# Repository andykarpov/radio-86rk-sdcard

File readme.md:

# Адаптер SD-CARD для Радио-86РК_SRAM

Данный проект является развитием проекта адаптера SD-CARD  от **Vinxru** 

## Изменения в схеме и печатной плате
- Добавлен LDO регулятор LM1117 3v3
- Вместо резистивных делителей используется буфер HEF4050BT
- добавлен 26-контактный IDC разъем под кабель для сопряжения модуля с Радио-86РК_SRAM
- Добавлен 6-контактный разъем для программатора
- Вместо Atmega8L используется МК Atmega328P

Плата разработана в CAD Eagle 7.0 и выполнена в форм-факторе 5x5 см, что дает возможность заказать ее производство у китайцев. Пробная первая партия была заказана у [http://www.dfrobot.com](http://www.dfrobot.com).

Gerber-файлы для производства платы проходят валидацию по стандартам pcb-сервиса от dfrobot.com.

## Фото готового устройства

## BOM-list

Микросхемы:

- U1 - Atmega8L(A) (или Atmega328P, или аналогичный МК)

- U2 - HEF4050BT (или другого производителя, 4050 в SMD-корпусе)

- IC1 - LM1117-3.3V

Разъемы:

- CONN1 - 4UCon 19646 или аналогичный ([pdf](http://www.4uconnector.com/online/object/4udrawing/19608.pdf), [Sparkfun](https://www.sparkfun.com/products/12769), [noname разъем на ebay](http://www.ebay.com/itm/5-Pcs-SD-Memory-Card-Sockets-Connectors-Replacements-29-x-28-5-x-2-5mm-/291005194440?pt=UK_BOI_Electrical_Components_Supplies_ET&hash=item43c142e0c8))

- CONN2 - угловой 2x13-контактный IDC-разъем (шаг 2.54мм)

- CONN3 - вертикальный 2x3-контактный pin header (шаг 2.54мм)

Резисторы:

- R1 - 470 Ом, корпус 1206

Конденсаторы:

- C1, C2 - 10 мкФ, танталовые полярные, корпус 1206

- C3, C4 - 0.1 мкФ, керамические, корпус 1206

Светодиод:

- LED1 - цвет свечения какой нравится, корпус 1206

## Адаптация исходного кода

Автор оригинальной разработки подготовил файлы boot.rk, sdbios.rk и shell.rk для Радио-86РК (меняются, как минимум, адреса портов).

Прошивка микроконтроллера Atmega8L остается без изменений, можно спокойно заливать авторскую.

Если же проект собирается на базе Atmega328P, то за основу можно взять модифицированную по этот камень прошивку из данного репозитария, в директории *firmware/src/atmega328p*. Вся соль не только в изменившихся адресах портов этого камня, а также в смещении переменной rom, которая в оригинальной конфигурации сидела по адресу 0100h, а теперь сидит по адресу 0200h. 

Также оказалось, что коммандер **shell.rk** не совсем корректно работает с *адаптером PS/2 клавиатуры* и моей кривой клавиатурой с неполной поддержкой ScanCode Set 3, при вызове функции биоса **getch()** возвращает странные значения для кнопок курсора. Соответственно, пришлось придумать альтернативное решение управления курсором, а именно: клавиши **Q,A,O,P**. Модифицированная версия shell.rk расположена в директории *firmware/src/shell_rk/*.

### Fuse bits для МК

На сайте [http://www.engbedded.com/fusecalc/](http://www.engbedded.com/fusecalc/) можно посчитать fuse bits для Вашего МК. 
Необходимо выбрать 

- Internal RC OSC 8MHz, 
- убрать галочку Divide clock by 8 internally

Все остальное можно не трогать или по желанию (например параметры brown out detection).

## Полезные ссылки
- Обсуждение проекта на zx-pk.ru: [http://zx-pk.ru/showthread.php?t=24092](http://zx-pk.ru/showthread.php?t=24092)

- Тема в барахолке на zx-pk.ru: [http://zx-pk.ru/market/viewtopic.php?f=7&t=2567&p=24381](http://zx-pk.ru/market/viewtopic.php?f=7&t=2567&p=24381)

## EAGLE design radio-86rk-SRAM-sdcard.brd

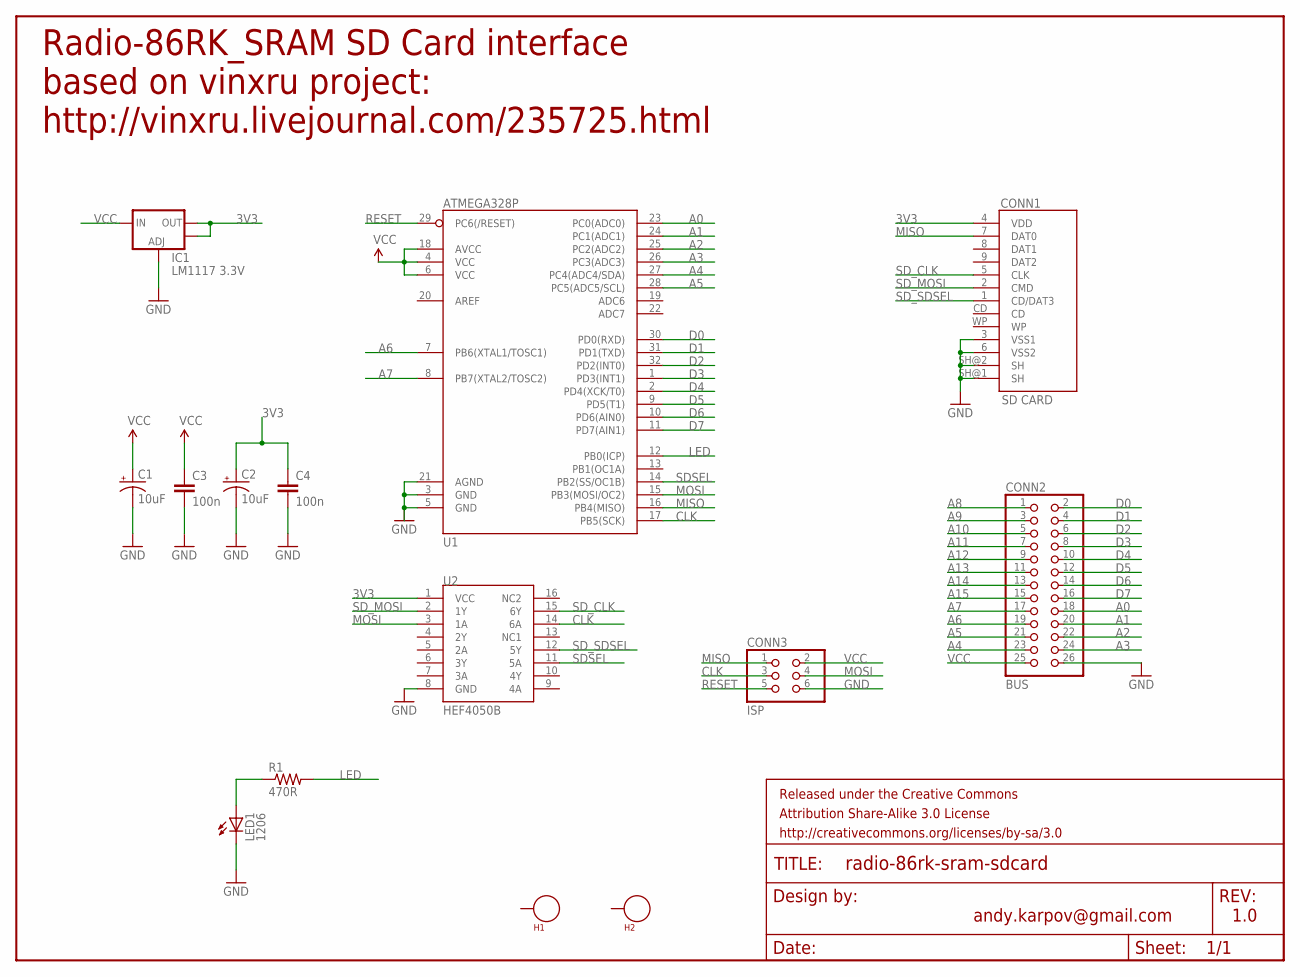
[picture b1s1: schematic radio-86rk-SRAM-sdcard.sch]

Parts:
C1, C2: 10uF; EIA3216
C3, C4: 100n; 1206
CONN1: SD CARD; SDCARD_4UCONN
CONN2: BUS; 2X13
CONN3: ISP; 2X03
FRAME1: FRAME-LETTER; CREATIVE_COMMONS
H1, H2: SEW_HOLE; SIMPLE_HOLE
IC1: LM1117 3.3V; SOT223
LED1: 1206; CHIPLED_1206
R1: 470R; 1206
U1: ATMEGA328P; TQFP32-08
U2: HEF4050B; SO16

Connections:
3V3: C2.A (+), C4.1, CONN1.4 (VDD), IC1.2 (OUT), IC1.4 (OUT), U2.1 (VCC)
A0: CONN2.18, U1.23 (PC0(ADC0))
A1: CONN2.20, U1.24 (PC1(ADC1))
A2: CONN2.22, U1.25 (PC2(ADC2))
A3: CONN2.24, U1.26 (PC3(ADC3))
A4: CONN2.23, U1.27 (PC4(ADC4/SDA))
A5: CONN2.21, U1.28 (PC5(ADC5/SCL))
A6: CONN2.19, U1.7 (PB6(XTAL1/TOSC1))
A7: CONN2.17, U1.8 (PB7(XTAL2/TOSC2))
A8: CONN2.1
A9: CONN2.3
A10: CONN2.5
A11: CONN2.7
A12: CONN2.9
A13: CONN2.11
A14: CONN2.13
A15: CONN2.15
CLK: CONN3.3, U1.17 (PB5(SCK)), U2.14 (6A)
D0: CONN2.2, U1.30 (PD0(RXD))
D1: CONN2.4, U1.31 (PD1(TXD))
D2: CONN2.6, U1.32 (PD2(INT0))
D3: CONN2.8, U1.1 (PD3(INT1))
D4: CONN2.10, U1.2 (PD4(XCK/T0))
D5: CONN2.12, U1.9 (PD5(T1))
D6: CONN2.14, U1.10 (PD6(AIN0))
D7: CONN2.16, U1.11 (PD7(AIN1))
GND: C1.C (-), C2.C (-), C3.2, C4.2, CONN1.3 (VSS1), CONN1.6 (VSS2), CONN1.SH@1 (SH), CONN1.SH@2 (SH), CONN2.26, CONN3.6, IC1.1 (ADJ), LED1.C, U1.3 (GND), U1.5 (GND), U1.21 (AGND), U2.8 (GND)
LED: R1.2, U1.12 (PB0(ICP))
MISO: CONN1.7 (DAT0), CONN3.1, U1.16 (PB4(MISO))
MOSI: CONN3.4, U1.15 (PB3(MOSI/OC2)), U2.3 (1A)
unnamed: LED1.A, R1.1
RESET: CONN3.5, U1.29 (PC6(/RESET))
SDSEL: U1.14 (PB2(SS/OC1B)), U2.11 (5A)
SD_CLK: CONN1.5 (CLK), U2.15 (6Y)
SD_MOSI: CONN1.2 (CMD), U2.2 (1Y)
SD_SDSEL: CONN1.1 (CD/DAT3), U2.12 (5Y)
VCC: C1.A (+), C3.1, CONN2.25, CONN3.2, IC1.3 (IN), U1.4 (VCC), U1.6 (VCC), U1.18 (AVCC)

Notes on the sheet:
Radio-86RK_SRAM SD Card interface based on vinxru project: http://vinxru.livejournal.com/235725.html
andy.karpov@gmail.com
1.0

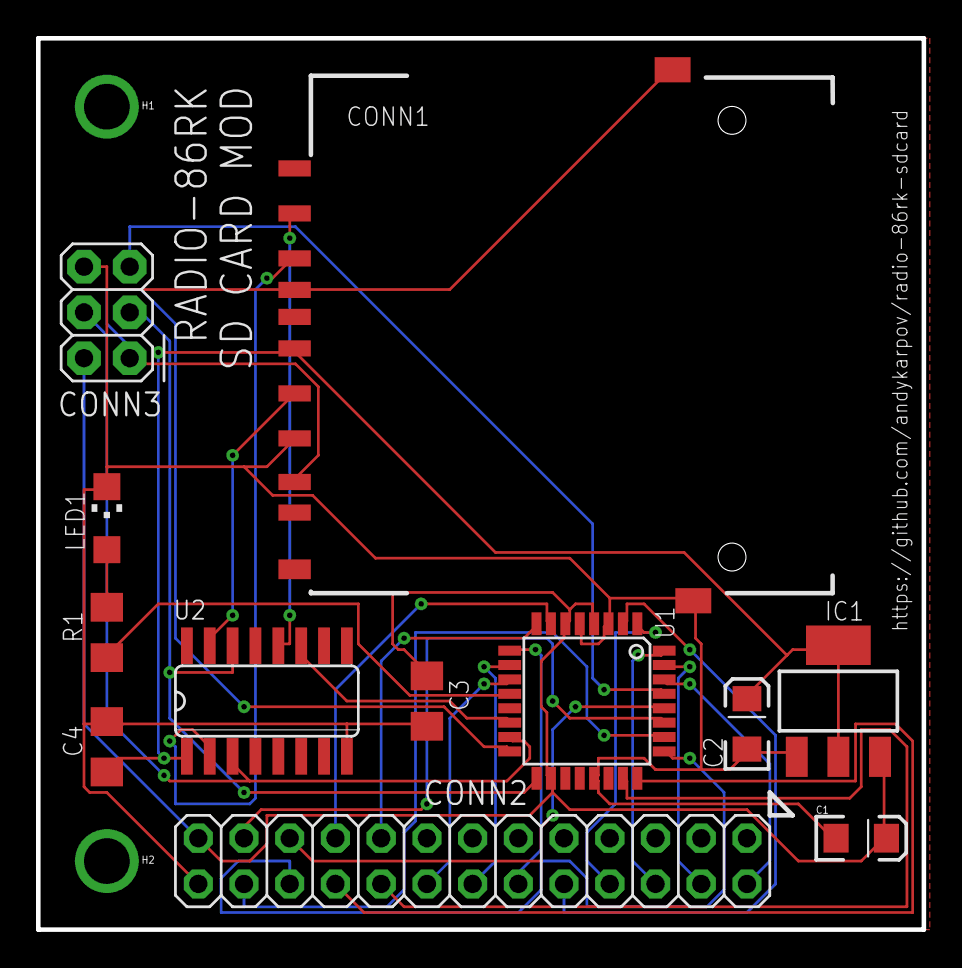
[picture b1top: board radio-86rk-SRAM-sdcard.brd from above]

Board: 2 copper layers, 49.2 x 49.5 mm, 15 parts (0 on the bottom side), 29 nets.

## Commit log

2014-10-06 added gerbers
2014-10-08 Добавлены библиотеки кастомных компонентов для Eagle
2014-10-08 Первая итерация перевода исходников прошивки контроллера на рельсы avr-gcc
2014-10-08 Подпрограмма эмуляции ПЗУ вынесена в отдельный файл rom_emu.S и подключена в Makefile
2014-10-08 Removed some strict warnings
2014-11-10 Изменения под Atmega328p + мелкие фиксы в работе коммандера
2014-11-10 Убрана неработающая песочница по переносу проекта на рельсы avrgcc
2014-11-10 Добавлены полезные ссылки
2014-11-10 Добавлено упоминание про gerbers
2014-11-10 Добавлен hotfix, если от PS/2 контроллера пришел залипший где-то в проводах сигнал нажатия клавиши enter
2014-11-15 Добавлен BOM-лист, мелкие фиксы
2016-11-29 Обновлен readme, добавлены исходники компилятора и архив утраченного проекта vinxru (спасибо cy6)
2016-11-29 Описание работы проекта от автора

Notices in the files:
parts and their libraries:
SparkFun-PowerIC: Licensing: CC v3.0 Share-Alike You are welcome to use this library for commercial purposes.
SparkFun-Aesthetics: Released under the Creative Commons Attribution Share-Alike 3.0 License
SparkFun-Aesthetics: http://creativecommons.org/licenses/by-sa/3.0
